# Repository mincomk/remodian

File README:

Remodian
============

Remodian (Remote Meridian) is a simple clone of a IR remote controller in Meridian 7000 audio system.

PlatformIO and `just` are the dependencies. Refer `justfile` to understand the building procedure.

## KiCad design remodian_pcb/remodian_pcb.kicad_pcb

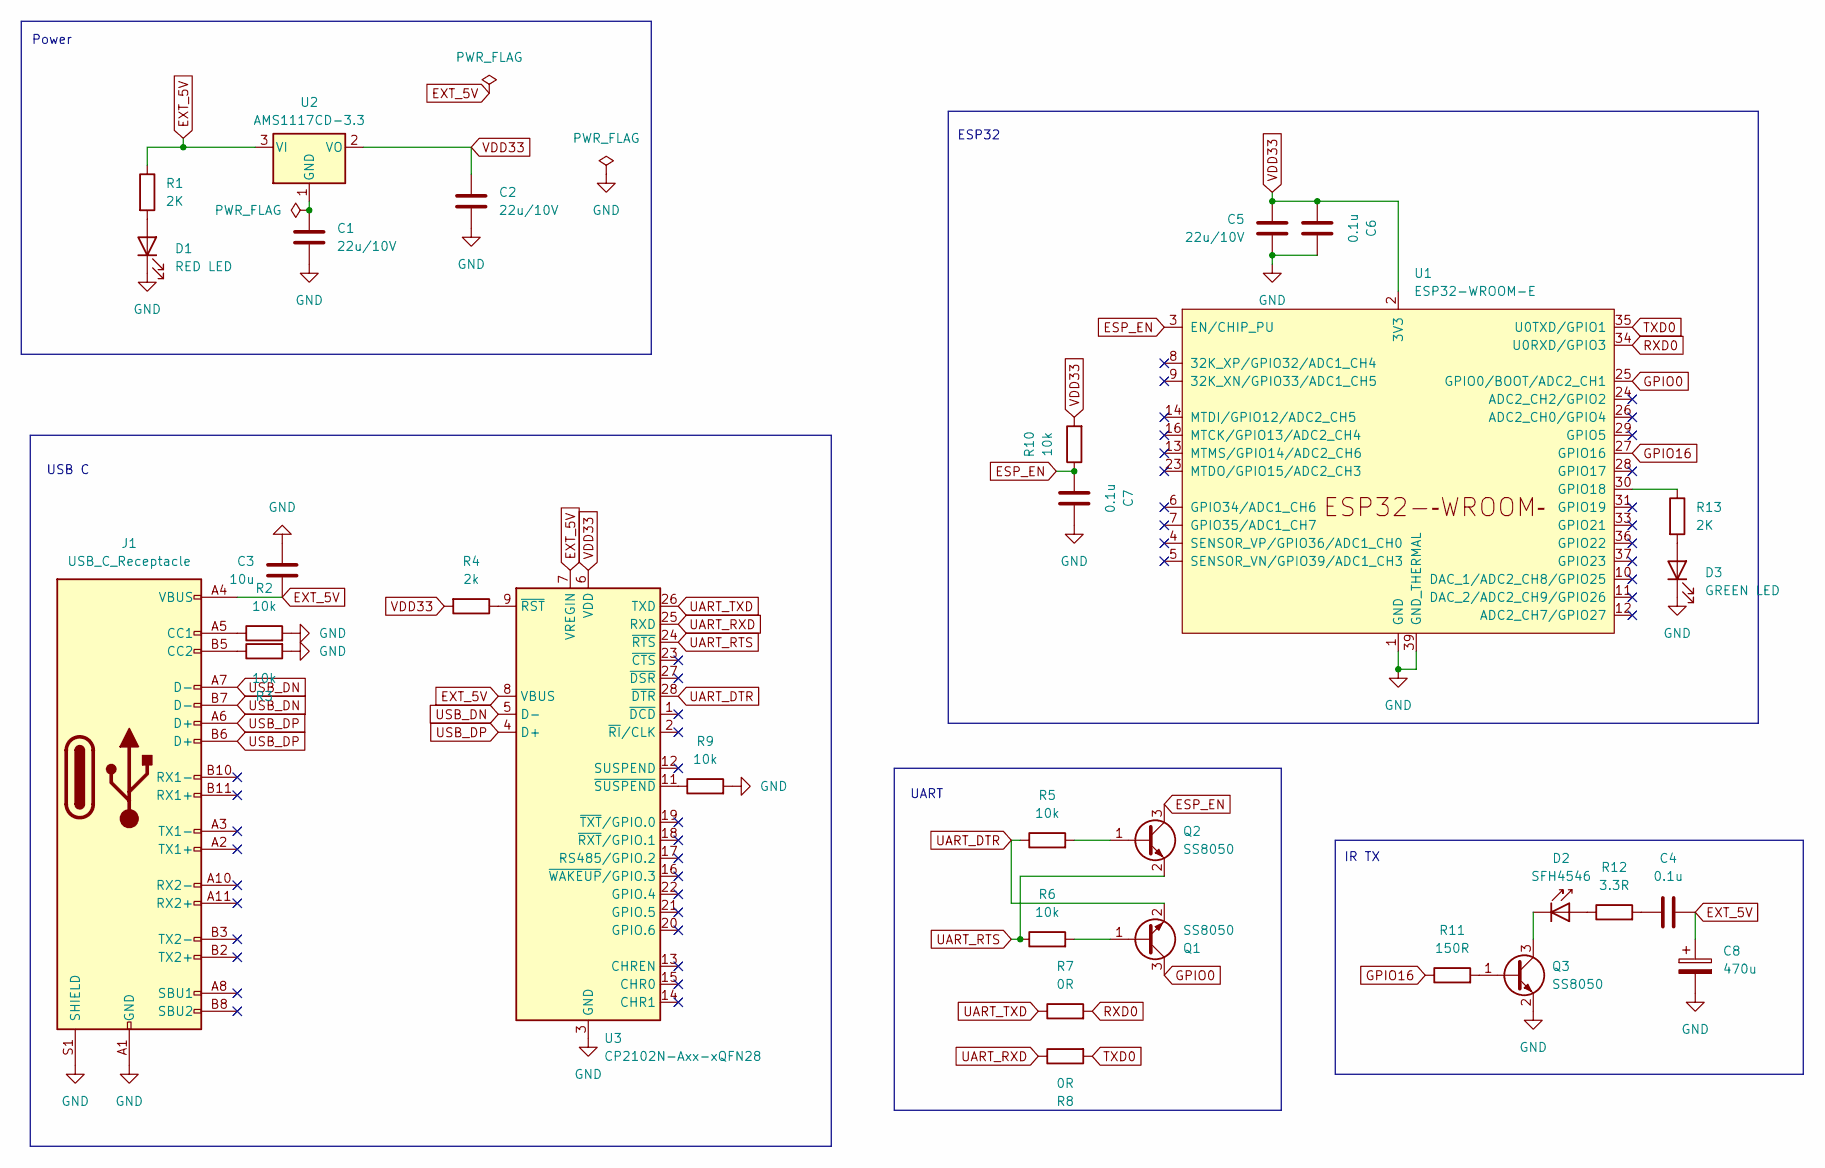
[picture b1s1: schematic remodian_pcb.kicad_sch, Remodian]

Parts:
C1, C2, C5: 22u/10V; C_0805_2012Metric
C3: 10u; C_0805_2012Metric
C4, C6, C7: 0.1u; C_0805_2012Metric
C8: 470u; CP_Radial_D5.0mm_P2.50mm
D1: RED LED; LED_0201_0603Metric
D2: SFH4546; LED_D5.0mm_IRGrey
D3: GREEN LED; LED_0201_0603Metric
J1: USB_C_Receptacle; USB_C_Receptacle_Amphenol_12401548E4-2A
Q1, Q2, Q3: SS8050; SOT-23
R1, R13: 2K; R_0201_0603Metric
R2, R3, R5, R6, R9, R10: 10k; R_0201_0603Metric
R4: 2k; R_0201_0603Metric
R7, R8: 0R; SolderJumper-2_P1.3mm_Bridged_Pad1.0x1.5mm
R11: 150R; R_0805_2012Metric
R12: 3.3R; R_0805_2012Metric
U1: ESP32-WROOM-E; ESP32-WROOM-32E
U2: AMS1117CD-3.3; TO-252-3_TabPin2
U3: CP2102N-Axx-xQFN28; QFN-28-1EP_5x5mm_P0.5mm_EP3.35x3.35mm

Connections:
ESP_EN: C7.2, Q2.3 (C), R10.1, U1.3 (EN/CHIP_PU)
EXT_5V: C3.1, C4.2, C8.1, J1.A4 (VBUS), J1.A9 (VBUS), J1.B4 (VBUS), J1.B9 (VBUS), R1.1, U2.3 (VI), U3.7 (VREGIN), U3.8 (VBUS)
GND: C1.2, C2.2, C3.2, C5.2, C6.1, C7.1, C8.2, D1.1 (K), D3.1 (K), J1.A1 (GND), J1.A12 (GND), J1.B1 (GND), J1.B12 (GND), J1.S1 (SHIELD), Q3.2 (E), R2.2, R3.2, R9.2, U1.1 (GND), U1.15 (GND), U1.38 (GND), U1.39 (GND_THERMAL), U3.3 (GND), U3.29 (GND)
GPIO0: Q1.3 (C), U1.25 (GPIO0/BOOT/ADC2_CH1)
GPIO16: R11.1, U1.27 (GPIO16)
unnamed: C4.1, R12.2
unnamed: D1.2 (A), R1.2
unnamed: D2.2 (A), R12.1
unnamed: D2.1 (K), Q3.3 (C)
unnamed: D3.2 (A), R13.2
unnamed: J1.A5 (CC1), R2.1
unnamed: J1.B5 (CC2), R3.1
unnamed: Q1.1 (B), R6.2
unnamed: Q2.1 (B), R5.2
unnamed: Q3.1 (B), R11.2
unnamed: R13.1, U1.30 (GPIO18)
unnamed: C1.1, U2.1 (GND)
unnamed: R4.1, U3.9 (~RST)
unnamed: R9.1, U3.11 (~SUSPEND)
RXD0: R7.2, U1.34 (U0RXD/GPIO3)
TXD0: R8.2, U1.35 (U0TXD/GPIO1)
UART_DTR: Q1.2 (E), R5.1, U3.28 (~DTR)
UART_RTS: Q2.2 (E), R6.1, U3.24 (~RTS)
UART_RXD: R8.1, U3.25 (RXD)
UART_TXD: R7.1, U3.26 (TXD)
USB_DN: J1.A7 (D-), J1.B7 (D-), U3.5 (D-)
USB_DP: J1.A6 (D+), J1.B6 (D+), U3.4 (D+)
VDD33: C2.1, C5.1, C6.2, R4.2, R10.2, U1.2 (3V3), U2.2 (VO), U3.6 (VDD)

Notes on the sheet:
USB C
IR TX
Power
UART
ESP32

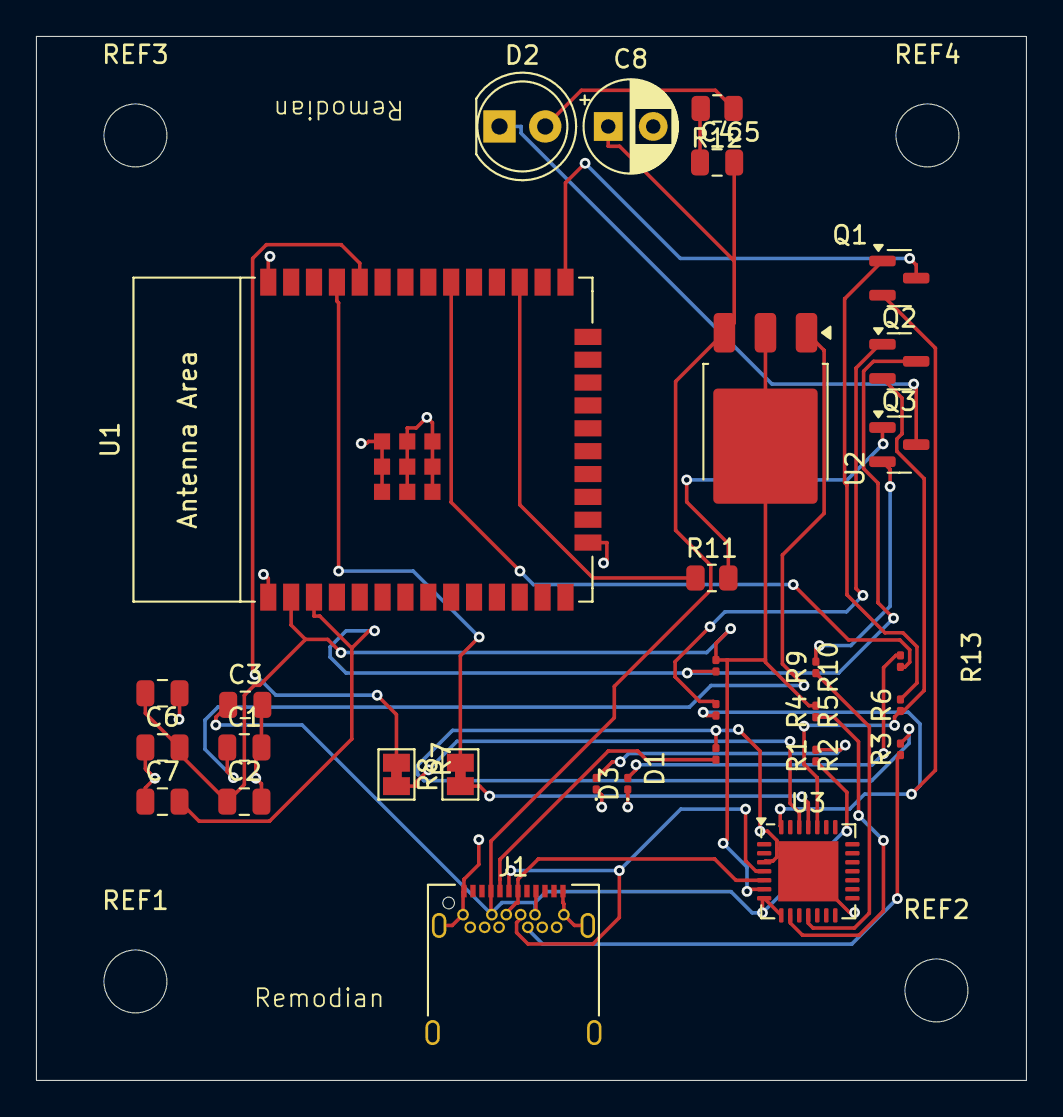
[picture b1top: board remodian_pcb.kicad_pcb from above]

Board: 2 copper layers, 55.0 x 58.0 mm, 35 parts (0 on the bottom side), 28 nets.

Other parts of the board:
REF1, REF2, REF3, REF4: MountingHole_3.5mm

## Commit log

2025-11-01 initial commit two
2025-11-01 chore: we don't test!
2025-11-01 chore: remove compile_commands
2025-11-02 chore: add IRRemote
2025-11-02 chore: signal analysis
2025-11-02 feat: firmware implementation
2025-11-02 refactor: make a space for web
2025-11-02 feat: add frontend
2025-11-02 feat: add docker
2025-11-02 chore: remove version field
2025-11-02 fix(ci): reflect moved firmware dir
2025-11-02 fix: fix vite env issue
2025-11-02 feat: add hybrid IR\
2025-11-02 refactor: organize some folders
2025-11-02 feat: add base pcb
2025-11-02 feat: add fab
2025-11-02 fix: change color
2025-11-02 refactor: move env
2025-11-03 feat: add PWA
2025-11-03 refactor: .env.example
2025-11-03 chore: .gitignore
